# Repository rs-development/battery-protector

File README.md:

# battery-protector
Battery under voltage protector circuit with integrated DCDC, Makita compatible

Work in progress

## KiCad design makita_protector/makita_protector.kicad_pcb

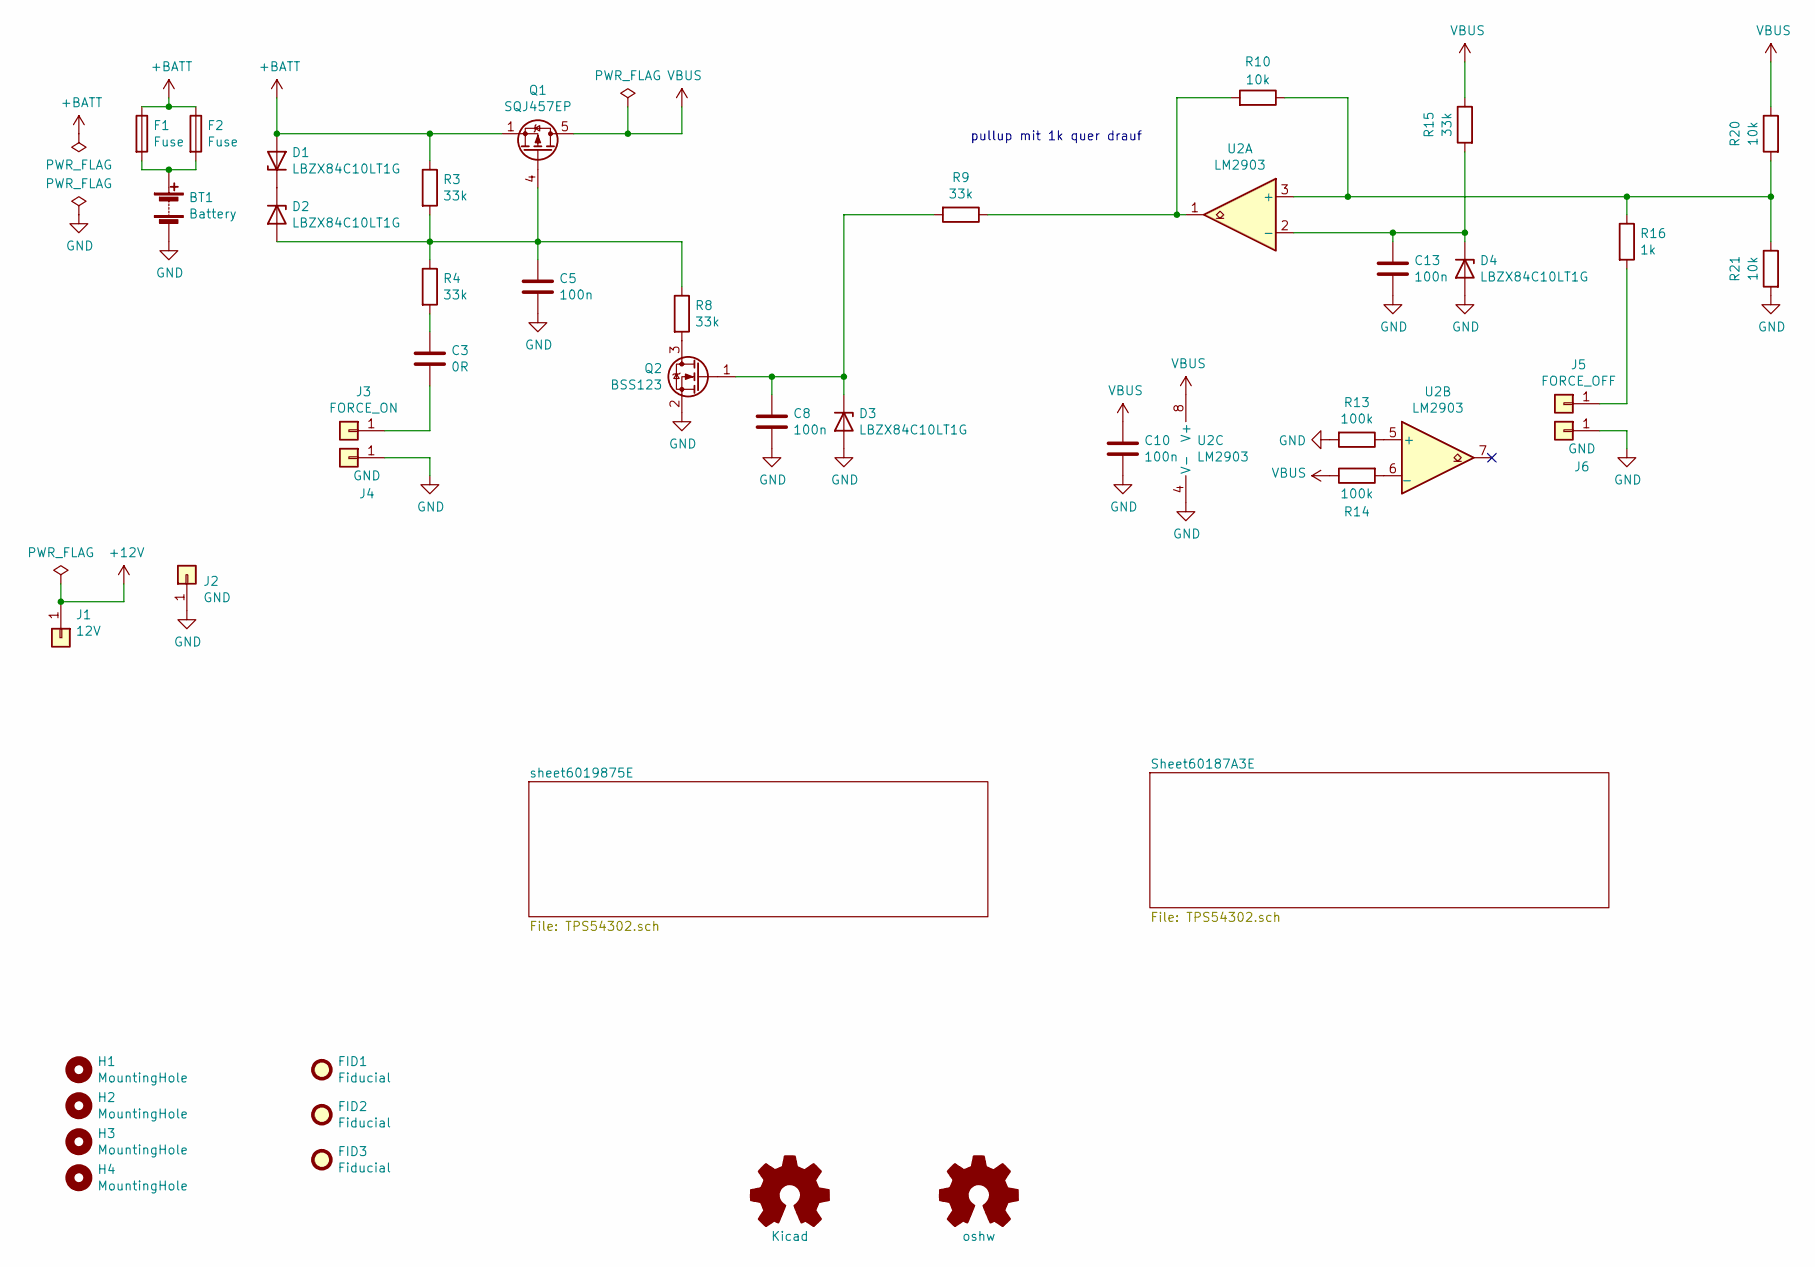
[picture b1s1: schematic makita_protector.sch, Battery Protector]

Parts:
BT1: Battery; contact_plates
C3: 0R; C_0805_2012Metric
C5, C8, C10, C13: 100n; C_0805_2012Metric
D1, D2, D3, D4: LBZX84C10LT1G; D_SOT-23_ANK
F1: Fuse; Fuse_1206_3216Metric
F2: Fuse; Fuse_0603_1608Metric
FID1, FID2, FID3: Fiducial; Fiducial_1mm_Mask2mm_Paste
H1, H2, H3, H4: MountingHole; MountingHole_3.2mm_M3_DIN965
J1: 12V; TestPoint_Plated_Hole_D2.0mm
J2, J4, J6: GND; TestPoint_Plated_Hole_D2.0mm
J3: FORCE_ON; TestPoint_Plated_Hole_D2.0mm
J5: FORCE_OFF; TestPoint_Plated_Hole_D2.0mm
LOGO1: oshw; OSHW-Logo2_7.3x6mm_SilkScreen
LOGO2: Kicad; KiCad-Logo2_5mm_SilkScreen
Q1: SQJ457EP; Vishay_PowerPAK_1212-8_Single
Q2: BSS123; SOT-23
R3, R4, R8, R9, R15: 33k; R_0805_2012Metric
R10, R20, R21: 10k; R_0805_2012Metric
R13, R14: 100k; R_0805_2012Metric
R16: 1k; R_0805_2012Metric
U2: LM2903; SOIC-8_3.9x4.9mm_P1.27mm

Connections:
+12V: J1.1; also elsewhere on the board
+BATT: D1.2 (A), F1.1, F2.1, Q1.1 (S), Q1.2 (S), Q1.3 (S), R3.1
GND: BT1.2 (-), C5.2, C8.2, C10.2, C13.2, D3.2 (A), D4.2 (A), J2.1, J4.1, J6.1, Q2.2 (S), R13.2, R21.2, U2.4 (V-); also elsewhere on the board
unnamed: BT1.1 (+), F1.2, F2.2
unnamed: C3.1, R4.2
unnamed: C3.2, J3.1
unnamed: C5.1, D2.2 (A), Q1.4 (G), R3.2, R4.1, R8.1
unnamed: C8.1, D3.1 (K), Q2.1 (G), R9.2
unnamed: C13.1, D4.1 (K), R15.2, U2.2 (-)
unnamed: D1.1 (K), D2.1 (K)
unnamed: J5.1, R16.2
unnamed: Q2.3 (D), R8.2
unnamed: R10.1, R16.1, R20.2, R21.1, U2.3 (+)
unnamed: R9.1, R10.2, U2.1
unnamed: R13.1, U2.5 (+)
unnamed: R14.2, U2.6 (_)
VBUS: C10.1, Q1.5 (D), R14.1, R15.1, R20.1, U2.8 (V+); also elsewhere on the board

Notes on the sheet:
pullup mit 1k quer drauf

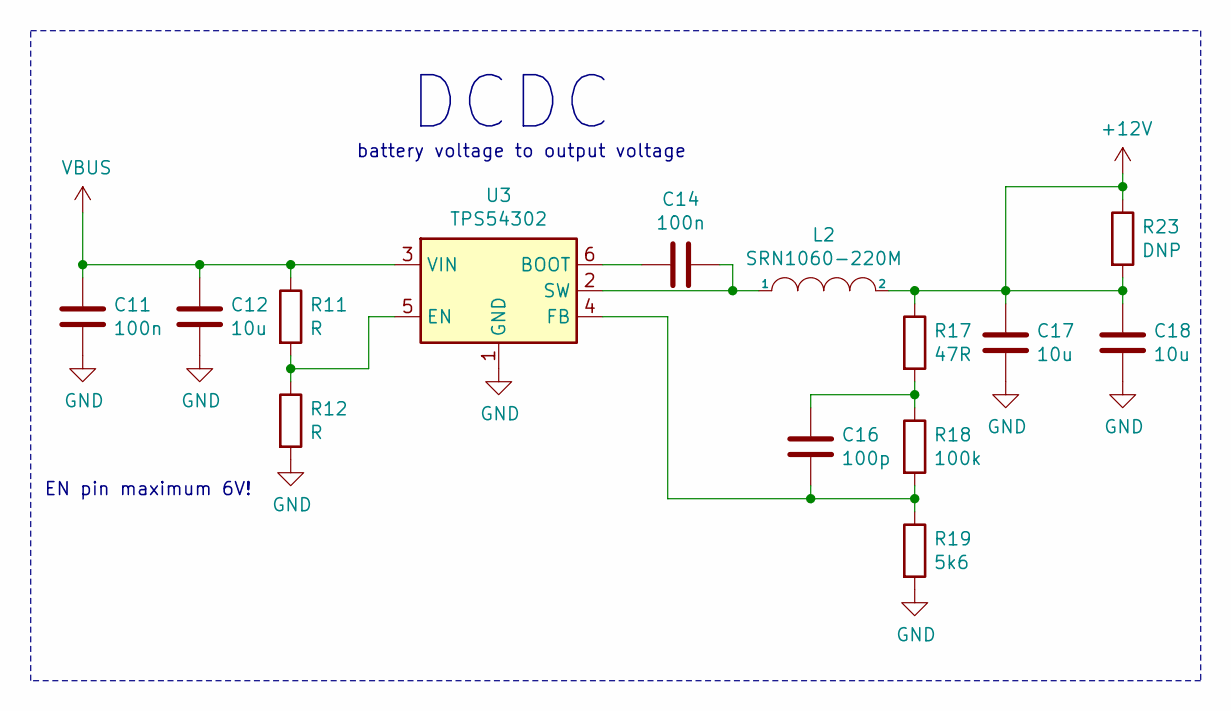
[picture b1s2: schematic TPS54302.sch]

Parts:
C1, C4: 100n; C_0805_2012Metric
C2, C7, C9: 10u; C_1206_3216Metric
C6: 100p; C_0805_2012Metric
L1: SRN1060-220M; L_Bourns-SRN1060
R1, R2: R; R_0805_2012Metric
R5: 47R; R_0805_2012Metric
R6: 100k; R_0805_2012Metric
R7: 5k6; R_0805_2012Metric
R23: DNP; R_0805_2012Metric
U1: TPS54302; SOT-23-6

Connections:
+12V: C7.1, C9.1, L1.2, R5.1, R23.1, R23.2; also elsewhere on the board
GND: C1.2, C2.2, C7.2, C9.2, R2.2, R7.2, U1.1 (GND); also elsewhere on the board
unnamed: C4.1, L1.1, U1.2 (SW)
unnamed: C4.2, U1.6 (BOOT)
unnamed: C6.1, R5.2, R6.1
unnamed: C6.2, R6.2, R7.1, U1.4 (FB)
unnamed: R1.2, R2.1, U1.5 (EN)
VBUS: C1.1, C2.1, R1.1, U1.3 (VIN); also elsewhere on the board

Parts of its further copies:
C11, C14: 100n; C_0805_2012Metric
C12, C17, C18: 10u; C_1206_3216Metric
C16: 100p; C_0805_2012Metric
L2: SRN1060-220M; L_Bourns-SRN1060
R11, R12: R; R_0805_2012Metric
R17: 47R; R_0805_2012Metric
R18: 100k; R_0805_2012Metric
R19: 5k6; R_0805_2012Metric
R22: DNP; R_0805_2012Metric
U3: TPS54302; SOT-23-6

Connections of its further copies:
+12V: C17.1, C18.1, L2.2, R17.1, R22.1, R22.2; also elsewhere on the board
GND: C11.2, C12.2, C17.2, C18.2, R12.2, R19.2, U3.1 (GND); also elsewhere on the board
unnamed: C14.1, L2.1, U3.2 (SW)
unnamed: C14.2, U3.6 (BOOT)
unnamed: C16.1, R17.2, R18.1
unnamed: C16.2, R18.2, R19.1, U3.4 (FB)
unnamed: R11.2, R12.1, U3.5 (EN)
VBUS: C11.1, C12.1, R11.1, U3.3 (VIN); also elsewhere on the board

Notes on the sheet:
EN pin maximum 6V!
DCDC
battery voltage to output voltage

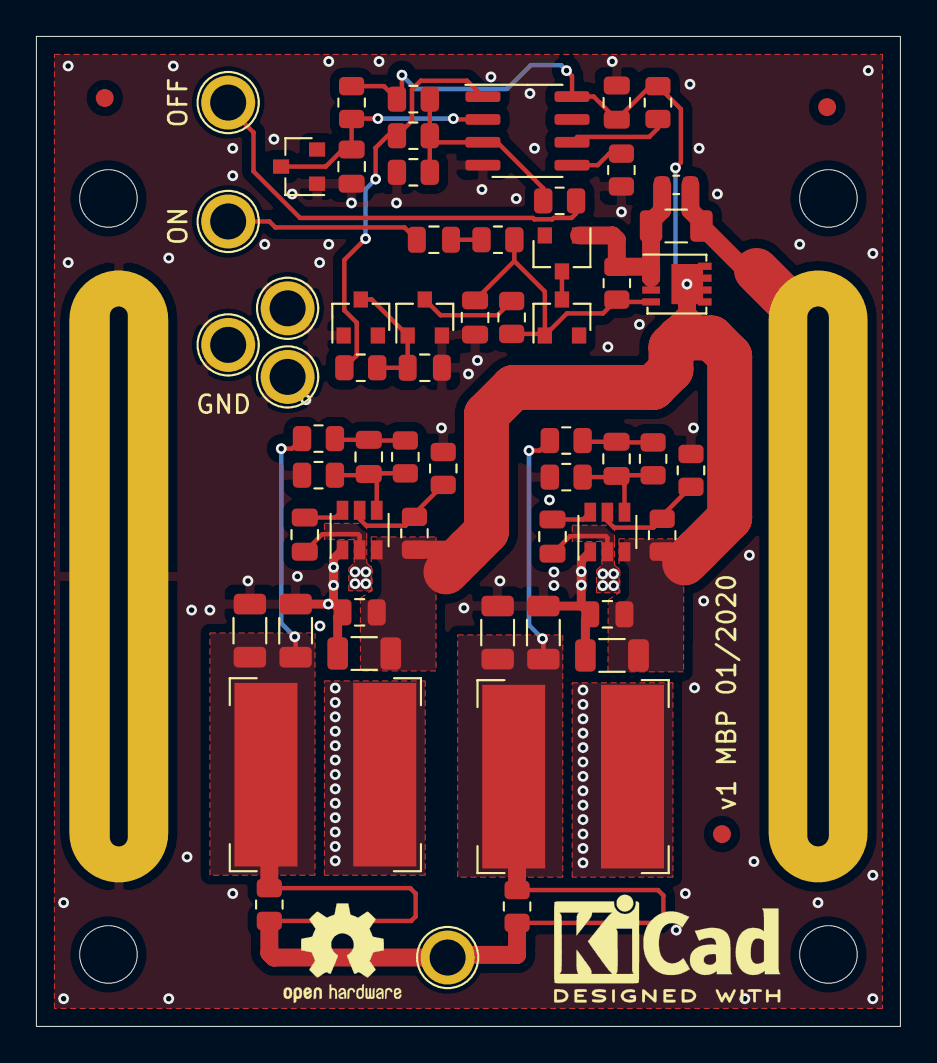
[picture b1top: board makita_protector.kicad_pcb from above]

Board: 2 copper layers, 48.0 x 55.0 mm, 69 parts (0 on the bottom side), 27 nets.

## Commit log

2021-01-13 first layout
2021-01-19 updated layput
2021-02-03 final version for production v1
2021-02-05 updated values after initial testing
